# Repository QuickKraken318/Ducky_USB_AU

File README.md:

Original project: https://github.com/Seytonic/malduino

Tried and tested with a transplanted ATMEGA32U4-AU

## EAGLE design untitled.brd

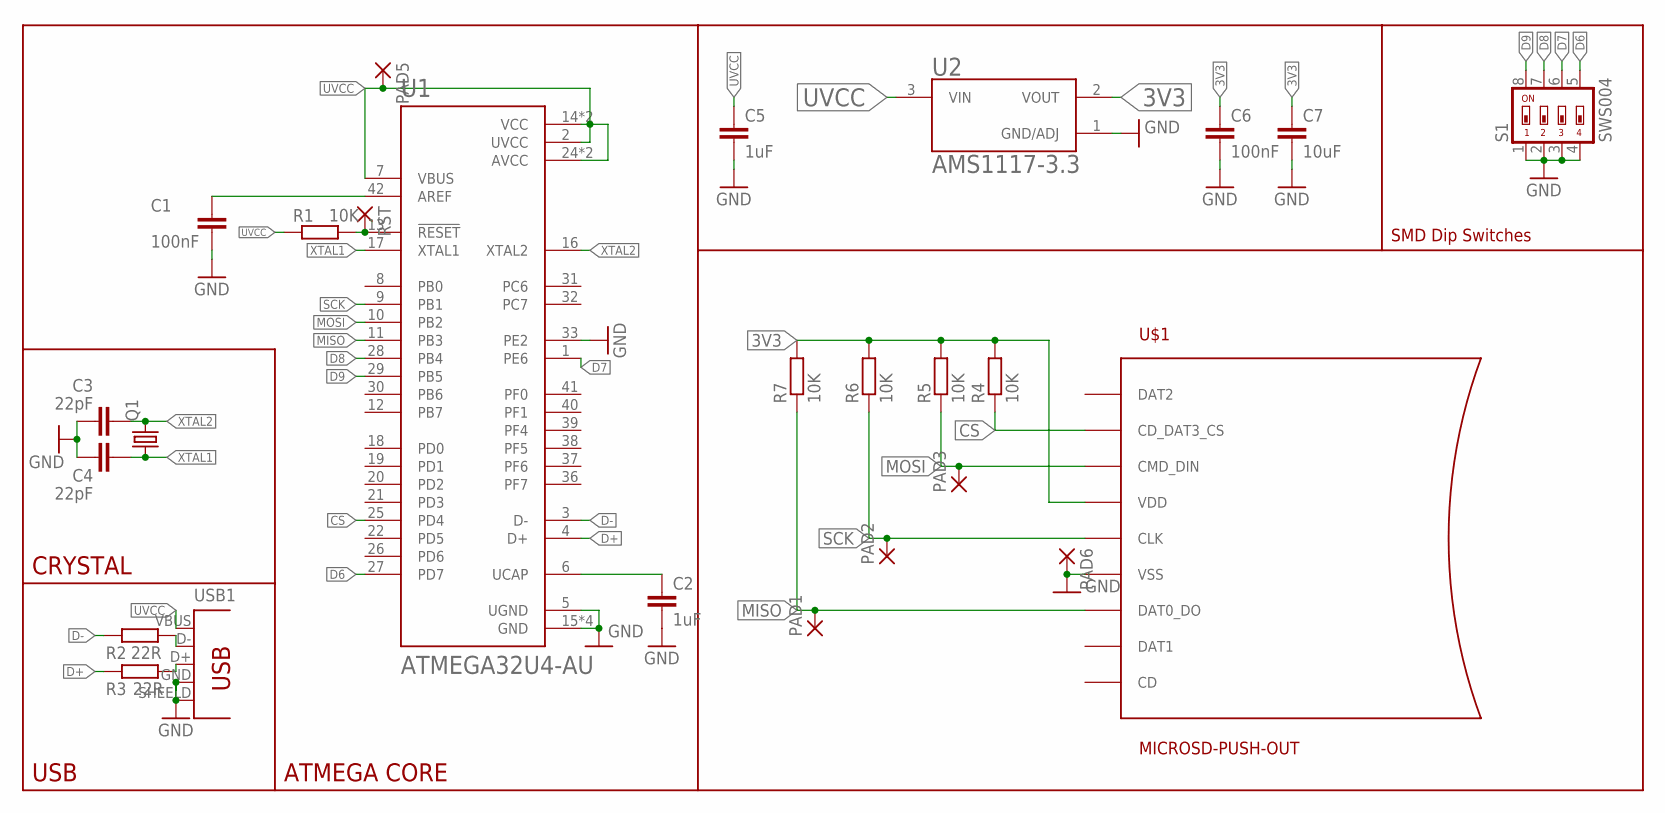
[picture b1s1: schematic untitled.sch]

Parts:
C1, C6: 100nF; C0603
C2, C5: 1uF; C0603
C3, C4: 22pF; C0603
C7: 10uF; C0603
PAD1, PAD2, PAD3, PAD5, PAD6: 1,6/0,8
Q1: CRYSTALCTS406; CTS406
R1, R4, R5, R6, R7: 10K; R0603
R2, R3: 22R; R0603
RST: 1,6/0,8
S1: SWS004; SMS-004
U1: ATMEGA32U4-AU; QFP80P1200X1200X120-44N
U2: AMS1117-3.3; SOT229P700X180-4N
U$1: MICROSD-PUSH-OUT
USB1: TYPE-A-MALE-SHILED; TYPE-A-MALE

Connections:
3V3: C6.1, C7.1, R4.2, R5.2, R6.2, R7.2, U2.2 (VOUT), U$1.4 (VDD)
CS: R4.1, U1.25 (PD4), U$1.2 (CD_DAT3_CS)
D6: S1.5, U1.27 (PD7)
D7: S1.6, U1.1 (PE6)
D8: S1.7, U1.28 (PB4)
D9: S1.8, U1.29 (PB5)
D+: R3.1, U1.4 (D+)
D-: R2.1, U1.3 (D-)
GND: C1.2, C2.2, C3.1, C4.1, C5.2, C6.2, C7.2, PAD6.1, S1.1, S1.2, S1.3, S1.4, U1.5 (UGND), U1.15 (GND), U1.23 (GND), U1.33 (PE2), U1.35 (GND), U1.43 (GND), U2.1 (GND/ADJ), U$1.6 (VSS), U$1.G1 (VSS), U$1.G2 (VSS), U$1.G3 (VSS), U$1.G4 (VSS), USB1.GND (4), USB1.SHEELD (5)
MISO: PAD1.1, R7.1, U1.11 (PB3), U$1.7 (DAT0_DO)
MOSI: PAD3.1, R5.1, U1.10 (PB2), U$1.3 (CMD_DIN)
unnamed: R2.2, USB1.D- (2)
unnamed: C1.1, U1.42 (AREF)
unnamed: C2.1, U1.6 (UCAP)
unnamed: R3.2, USB1.D+ (3)
RST: R1.2, RST.1, U1.13 (!RESET)
SCK: PAD2.1, R6.1, U1.9 (PB1), U$1.5 (CLK)
UVCC: C5.1, PAD5.1, R1.1, U1.2 (UVCC), U1.7 (VBUS), U1.14 (VCC), U1.24 (AVCC), U1.34 (VCC), U1.44 (AVCC), U2.3 (VIN), USB1.VBUS (1)
XTAL1: C4.2, Q1.1, U1.17 (XTAL1)
XTAL2: C3.2, Q1.3 (2), U1.16 (XTAL2)

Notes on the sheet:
CRYSTAL
USB
ATMEGA CORE
SMD Dip Switches

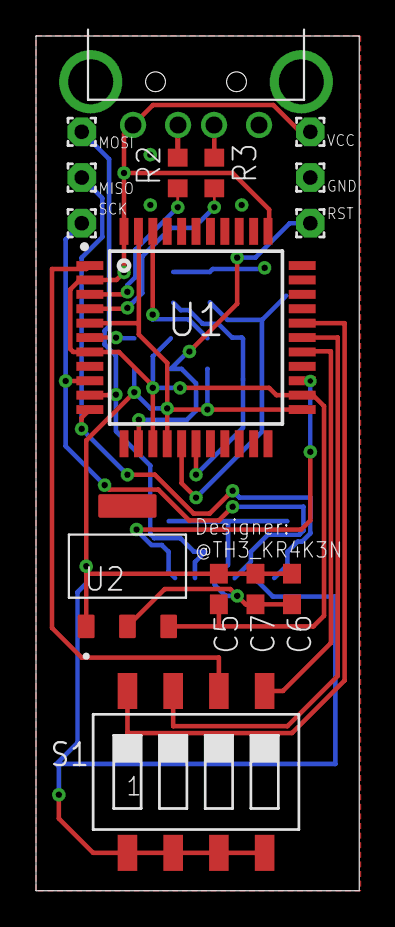
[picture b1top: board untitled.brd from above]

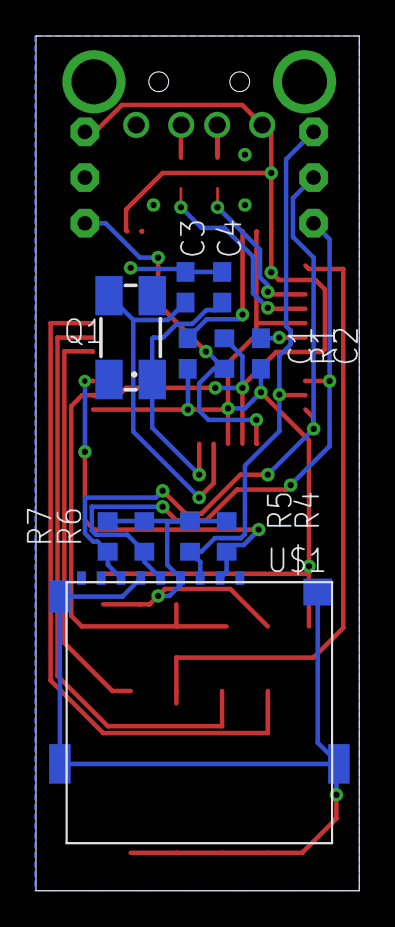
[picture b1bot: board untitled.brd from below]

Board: 2 copper layers, 18.0 x 47.5 mm, 26 parts (11 on the bottom side), 20 nets.

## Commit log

2025-04-05 Create a
